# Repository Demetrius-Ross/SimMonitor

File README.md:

# SimMonitoring Overview WIP

Rename the main script to main.py
'''bash
mv espnow_sender_relay.py main.py
'''

Flash it to the ESP32:
'''bash
mpremote connect /dev/ttyUSB0 fs cp main.py :
'''

Reset the ESP32 to run it automatically:
'''bash
mpremote connect /dev/ttyUSB0 reset
'''

If you want manual execution, you can run any script interactively:
'''bash
mpremote connect /dev/ttyUSB0 run gpio_test.py
'''

## Wiring Guide for Each ESP32 Device

# ESP32 Device ID Configuration for Sender

Below is a quick reference for how to wire **GPIO17**, **GPIO16**, **GPIO4**, and **GPIO2** to assign a **device ID** (0–15). Each pin is interpreted as a bit in the 4-bit ID, read in the order `(Pin2=bit0, Pin4=bit1, Pin16=bit2, Pin17=bit3)`.

| Device ID | Binary (bit3..bit0) | Pin17 (bit3) | Pin16 (bit2) | Pin4 (bit1) | Pin2 (bit0) |
|-----------|----------------------|--------------|--------------|-------------|-------------|
| **0**     | `0000`              | 0 (LOW)      | 0 (LOW)      | 0 (LOW)     | 0 (LOW)     |
| **1**     | `0001`              | 0 (LOW)      | 0 (LOW)      | 0 (LOW)     | 1 (HIGH)    |
| **2**     | `0010`              | 0 (LOW)      | 0 (LOW)      | 1 (HIGH)    | 0 (LOW)     |
| **3**     | `0011`              | 0 (LOW)      | 0 (LOW)      | 1 (HIGH)    | 1 (HIGH)    |
| **4**     | `0100`              | 0 (LOW)      | 1 (HIGH)     | 0 (LOW)     | 0 (LOW)     |
| **5**     | `0101`              | 0 (LOW)      | 1 (HIGH)     | 0 (LOW)     | 1 (HIGH)    |
| **6**     | `0110`              | 0 (LOW)      | 1 (HIGH)     | 1 (HIGH)    | 0 (LOW)     |
| **7**     | `0111`              | 0 (LOW)      | 1 (HIGH)     | 1 (HIGH)    | 1 (HIGH)    |
| **8**     | `1000`              | 1 (HIGH)     | 0 (LOW)      | 0 (LOW)     | 0 (LOW)     |
| **9**     | `1001`              | 1 (HIGH)     | 0 (LOW)      | 0 (LOW)     | 1 (HIGH)    |
| **10**    | `1010`              | 1 (HIGH)     | 0 (LOW)      | 1 (HIGH)    | 0 (LOW)     |
| **11**    | `1011`              | 1 (HIGH)     | 0 (LOW)      | 1 (HIGH)    | 1 (HIGH)    |
| **12**    | `1100`              | 1 (HIGH)     | 1 (HIGH)     | 0 (LOW)     | 0 (LOW)     |
| **13**    | `1101`              | 1 (HIGH)     | 1 (HIGH)     | 0 (LOW)     | 1 (HIGH)    |
| **14**    | `1110`              | 1 (HIGH)     | 1 (HIGH)     | 1 (HIGH)    | 0 (LOW)     |
| **15**    | `1111`              | 1 (HIGH)     | 1 (HIGH)     | 1 (HIGH)    | 1 (HIGH)    |

## Notes

1. **GPIO2** is the **least significant bit** (bit0).  
2. **GPIO17** is the **most significant bit** (bit3).  
3. Use **10kΩ resistors** (or internal pulls) to pull each pin HIGH or LOW.  
4. For a **Sender** role, set **GPIO18 = 0 (LOW)** and **GPIO19 = 0 (LOW)**. This yields `role_value = 0` => `"SENDER"`.

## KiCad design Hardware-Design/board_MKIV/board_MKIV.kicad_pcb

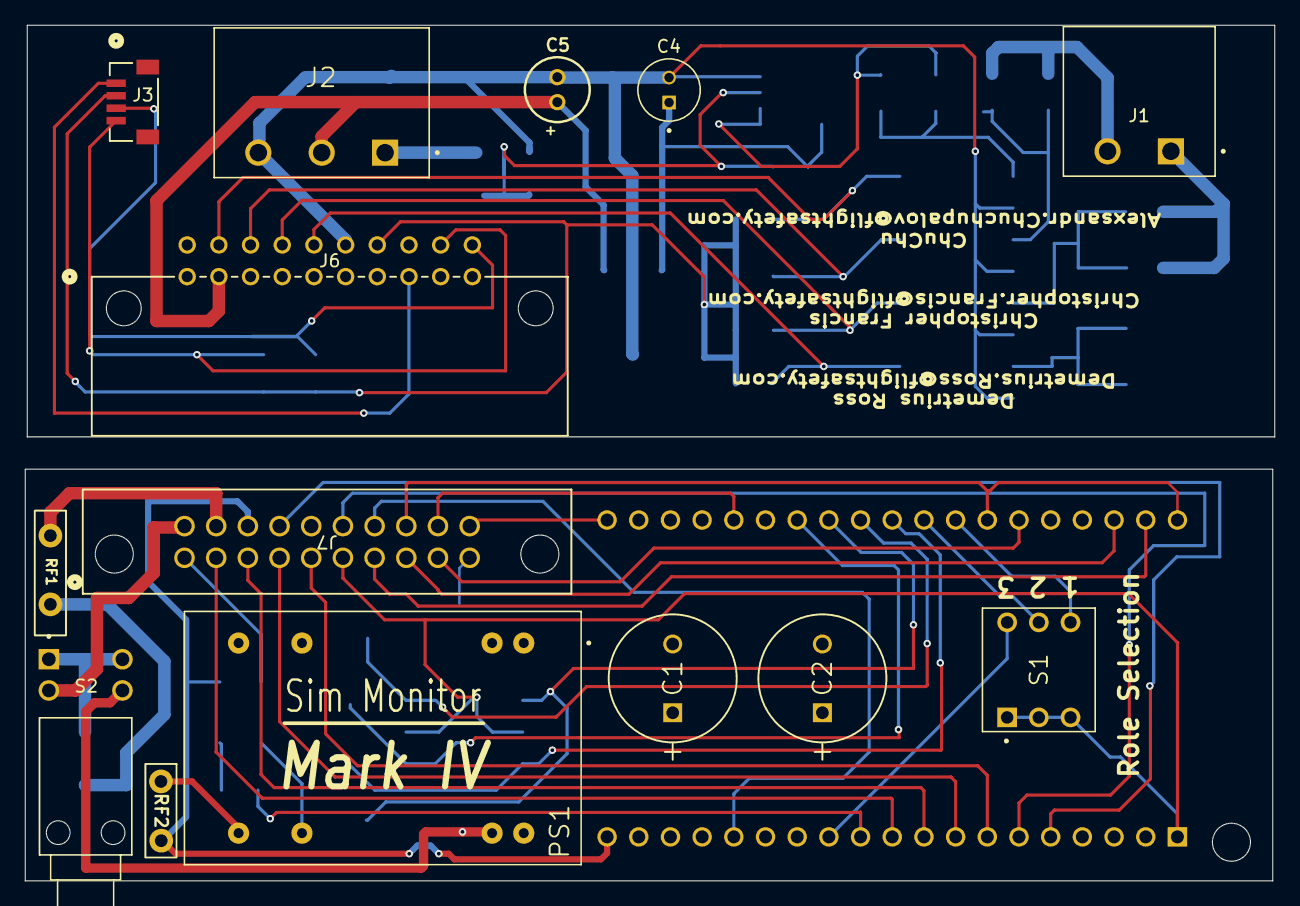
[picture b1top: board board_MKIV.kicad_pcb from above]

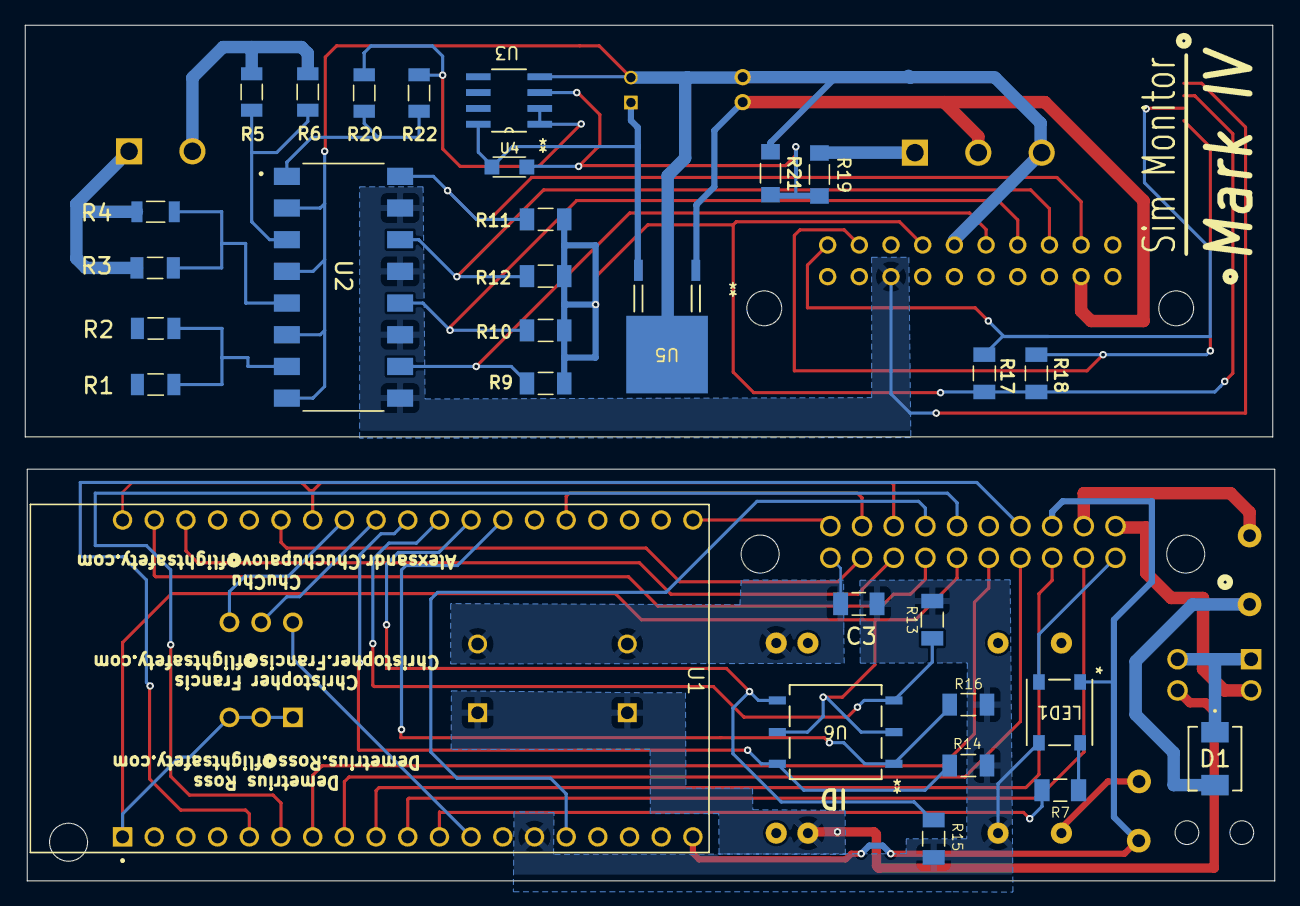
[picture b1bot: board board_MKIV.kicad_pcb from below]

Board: 2 copper layers, 100.2 x 68.6 mm, 44 parts (30 on the bottom side), 40 nets.

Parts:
C1, C2: UHE2A470MPD; PCAP_10x12_5-THRU-ELECT_NCA
C3: 1000pf/3kV; CAPC3216X180N
C4: ECA1HM100; CAPPRD200W50D500H1100
C5: WCAP-ATG5_5X11; WCAP-ATG5_5X11_DXL_
D1: SS34B-HF; DO214AASMB_CIP-L
J1: 1757242; PHOENIX_1757242
J2: jst-power; PHOENIX_1757255
J3: JST -SM; CONN_BM04B-SRSS-TB_SPK
J6: 20_pin_90
J7: 20-pin-straight; 20_pin_straight
LED1: COM-16347; COM-16347_SPK
PS1: REC5A-2405SW_H2; CONV_REC5A-2405SW_H2
R1, R2, R3, R5, R6: CRGH1206J4K7; RESC3115X65N
R4: CRGH1206J4K7; RESC3015X65N
R7: CRL1206-FW-R330ELF; RESC3216X70N
R9, R10, R11, R12, R13, R14, R15, R16, R17, R18: CR1206-FX-1002ELF; RESC3216X75N
R19: ERJP08J105V; RES_ERJP08J105V
R20, R22: CRG1206F470R; RESC3115X65N
R21: ERJP08J334V; RES_ERJP08J334V
RF1, RF2: PTC_RESET_FUSE
S1: DS01C-254-S-03BE; SW_DS01C-254-S-03BE
S2: PB400EEQR1BLK; SW_PB400EEQR1BLK
U1: ESP32-DEVKITC-32D; MODULE_ESP32-DEVKITC-32D
U2: LTV-846S; SOIC254P1016X460-16N
U3: TLV272CDR; D8
U4: BAT46W; SOD123F
U5: BA&; TO252-3_ROM
U6: SH-7070TB; SH-7070TB_7P1X7P3_NDC

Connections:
+3.3V: J3.2, J6.B7, J7.6, R9.2, R10.2, R11.2, R12.2, R17.1, R18.1, S1.1A, S1.2A, S1.3A, U1.J2-1 (3V3), U6.2, U6.5
+24V: D1.1, S2.1, S2.3
+VIN: C1.1, C2.1, D1.2, J6.A1, J7.11, PS1.22 (+VIN), RF1.2, S2.2, S2.4
+VIN-dc: C5.1, J2.02, J6.A2, J7.12, RF1.1, U5.1 (INPUT)
+VOUT_esp_signal: J6.A3, J7.13, LED1.1 (VDD), RF2.2, U1.J2-19 (EXT_5V)
-Vin: C1.2, C2.2, C3.2, C4.N, C5.2, J2.03, J6.B6, J7.10, PS1.2 (-VIN), R21.1, U2.2, U2.4, U2.6, U2.8, U3.4 (GND), U5.2 (Common)
/ESP-Board/+VOUT: PS1.14 (+VOUT), RF2.1
/ramp_down_opto: R5.2, R6.2, U2.3
/sim_home_opto: R20.2, R22.2, U2.1
CLK: J6.A10, J7.20, U1.J3-19 (CLK)
ESP_GND2: C3.1, J3.1, J6.A8, J7.18, LED1.3 (VSS), PS1.16 (-VOUT), R13.2, R14.2, R15.2, R16.2, U1.J2-14 (GND1), U1.J3-1 (GND3), U1.J3-7 (GND2), U2.9, U2.11, U2.13, U2.15
GPIO_2: J6.A9, J7.19, U1.J3-15 (IO2)
GPIO_4: R16.1, U1.J3-13 (IO4), U6.1
GPIO_5: R14.1, U1.J3-10 (IO5), U6.6
GPIO_13: J6.A7, J7.17, U1.J2-15 (IO13)
GPIO_14: S1.1B, U1.J2-12 (IO14)
GPIO_16: R15.1, U1.J3-12 (IO16), U6.4
GPIO_17: R13.1, U1.J3-11 (IO17), U6.3
GPIO_18: S1.2B, U1.J3-9 (IO18)
GPIO_19: S1.3B, U1.J3-8 (IO19)
GPIO_21: J3.3, J6.B10, J7.9, R17.2, U1.J3-6 (IO21)
GPIO_22: J3.4, J6.B9, J7.8, R18.2, U1.J3-3 (IO22)
GPIO_23: J6.B8, J7.7, U1.J3-2 (IO23)
GPIO_25: J6.B3, J7.3, R12.1, U1.J2-9 (IO25), U2.14
GPIO_26: J6.B2, J7.2, R11.1, U1.J2-10 (IO26), U2.16
GPIO_27: J6.B1, J7.1, LED1.2 (DOUT), R7.2, U1.J2-11 (IO27)
GPIO_32: J6.B5, J7.5, R9.1, U1.J2-7 (IO32), U2.10
GPIO_33: J6.B4, J7.4, R10.1, U1.J2-8 (IO33), U2.12
GPIO_ANAG_34: J6.A4, J7.14, U1.J2-5 (IO34)
GPIO_ANAG_35: J6.A6, J7.16, U1.J2-6 (IO35)
unnamed: LED1.4 (DIN), R7.1
unnamed: R19.1, R21.2, U3.3 (1IN+), U4.2
VDD: C4.P, U3.8 (VDD), U4.1, U5.3 (OUTPUT)
ramp_down: J1.02, R5.1, R6.1
ramp_up: J1.01, R3.1, R4.1
ramp_up_opto: R3.2, R4.2, U2.5
sim_home: J2.01, R19.2
sim_home_safe: R20.1, R22.1, U3.1 (1OUT), U3.2 (1IN-)
spare: R1.1, R2.1
spare_opto: R1.2, R2.2, U2.7

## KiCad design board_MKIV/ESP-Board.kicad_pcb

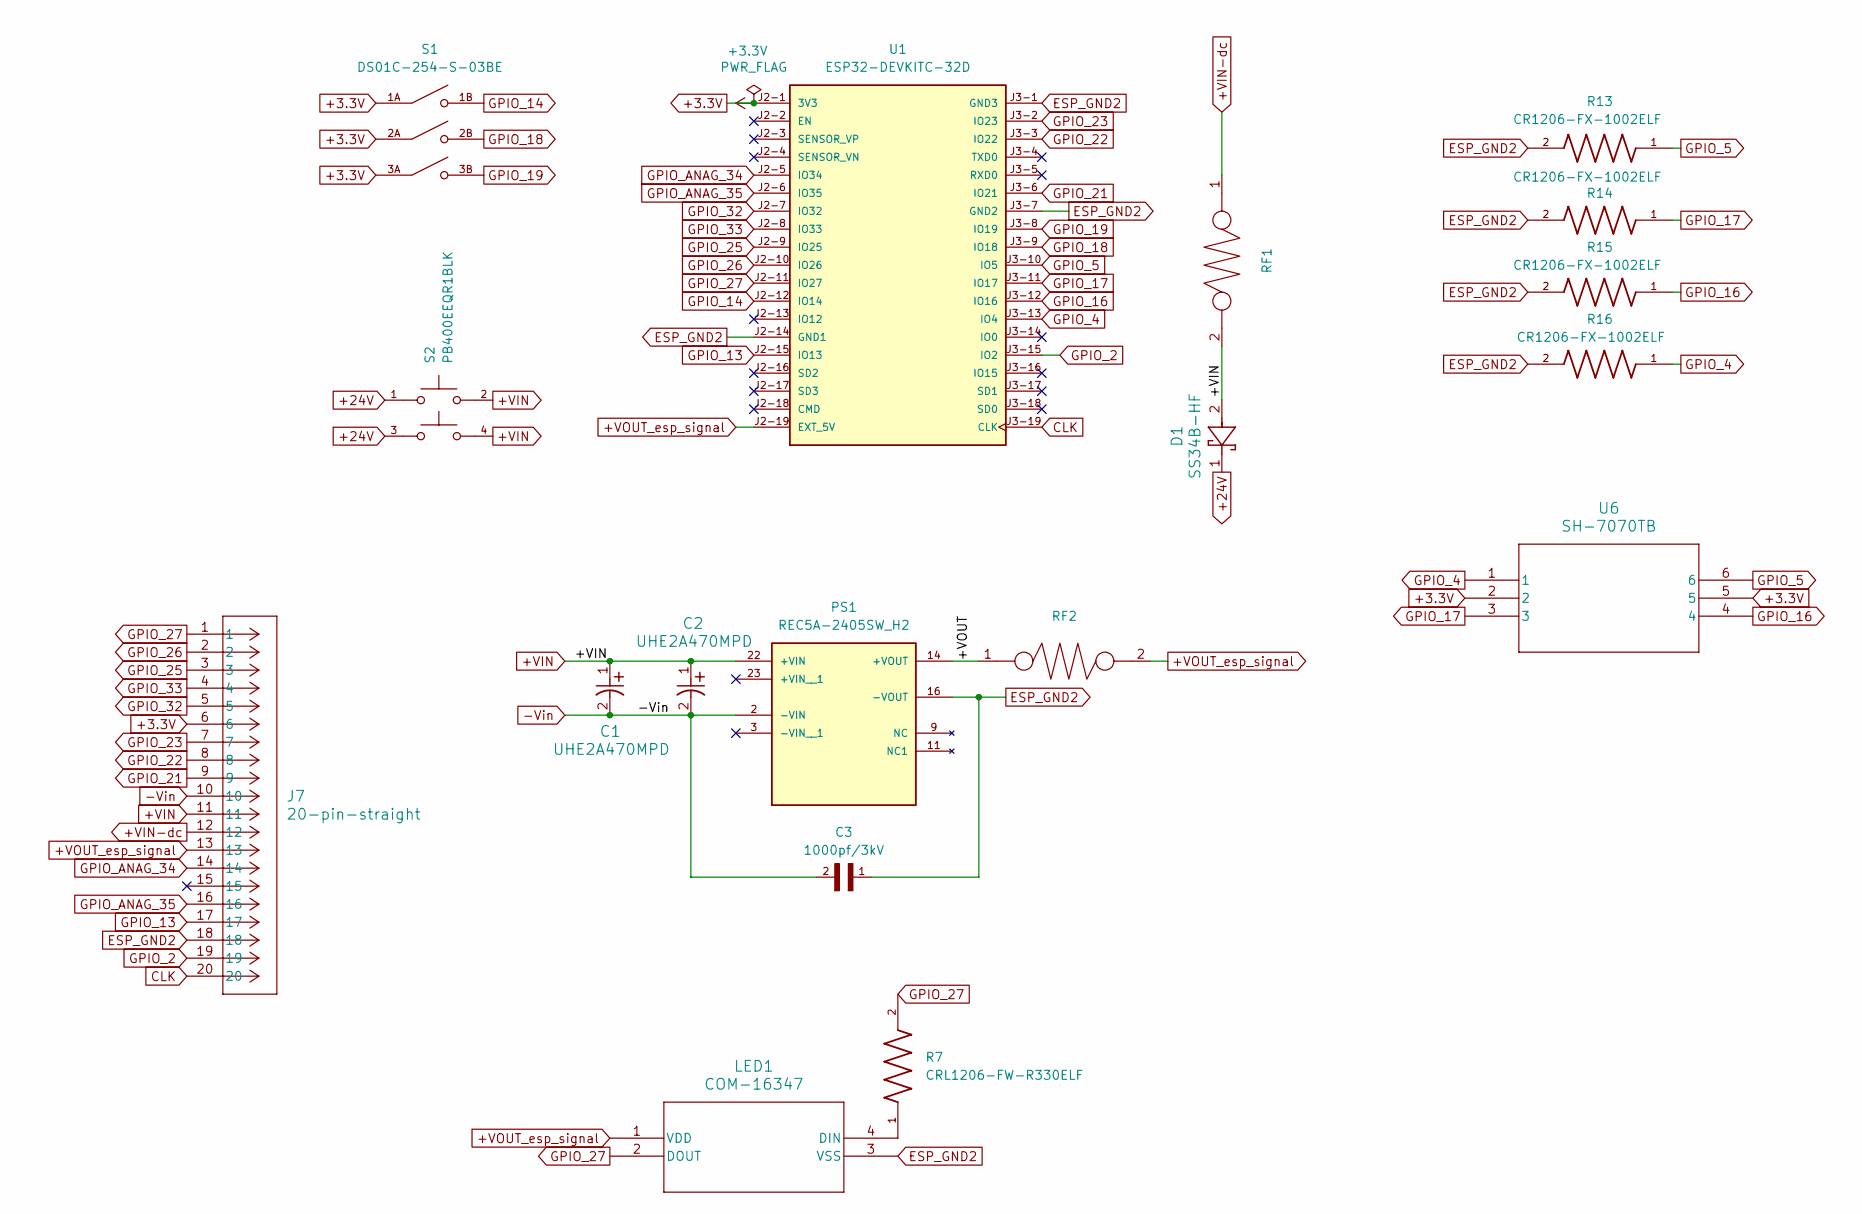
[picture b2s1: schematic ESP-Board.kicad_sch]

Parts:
C1, C2: UHE2A470MPD; PCAP_10x12_5-THRU-ELECT_NCA
C3: 1000pf/3kV; CAPC3216X180N
D1: SS34B-HF; DO214AASMB_CIP-L
J7: 20-pin-straight; 20_pin_straight
LED1: COM-16347; COM-16347_SPK
PS1: REC5A-2405SW_H2; CONV_REC5A-2405SW_H2; PARTREV N/A
R7: CRL1206-FW-R330ELF; RESC3216X70N
R13, R14, R15, R16: CR1206-FX-1002ELF; RESC3216X75N
RF1, RF2: PTC_RESET_FUSE
S1: DS01C-254-S-03BE; SW_DS01C-254-S-03BE; PARTREV 1.0
S2: PB400EEQR1BLK; SW_PB400EEQR1BLK; PARTREV A
U1: ESP32-DEVKITC-32D; MODULE_ESP32-DEVKITC-32D; PARTREV V4
U6: SH-7070TB; SH-7070TB_7P1X7P3_NDC

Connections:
+3.3V: J7.6, S1.1A, S1.2A, S1.3A, U1.J2-1 (3V3), U6.2, U6.5
+24V: D1.1, S2.1, S2.3
+VIN: C1.1, C2.1, D1.2, J7.11, PS1.22 (+VIN), RF1.2, S2.2, S2.4
+VIN-dc: J7.12, RF1.1
+VOUT_esp_signal: J7.13, LED1.1 (VDD), RF2.2, U1.J2-19 (EXT_5V)
-Vin: C1.2, C2.2, C3.2, J7.10, PS1.2 (-VIN)
/ESP-Board/+VOUT: PS1.14 (+VOUT), RF2.1
CLK: J7.20, U1.J3-19 (CLK)
ESP_GND2: C3.1, J7.18, LED1.3 (VSS), PS1.16 (-VOUT), R13.2, R14.2, R15.2, R16.2, U1.J2-14 (GND1), U1.J3-1 (GND3), U1.J3-7 (GND2)
GPIO_2: J7.19, U1.J3-15 (IO2)
GPIO_4: R16.1, U1.J3-13 (IO4), U6.1
GPIO_5: R14.1, U1.J3-10 (IO5), U6.6
GPIO_13: J7.17, U1.J2-15 (IO13)
GPIO_14: S1.1B, U1.J2-12 (IO14)
GPIO_16: R15.1, U1.J3-12 (IO16), U6.4
GPIO_17: R13.1, U1.J3-11 (IO17), U6.3
GPIO_18: S1.2B, U1.J3-9 (IO18)
GPIO_19: S1.3B, U1.J3-8 (IO19)
GPIO_21: J7.9, U1.J3-6 (IO21)
GPIO_22: J7.8, U1.J3-3 (IO22)
GPIO_23: J7.7, U1.J3-2 (IO23)
GPIO_25: J7.3, U1.J2-9 (IO25)
GPIO_26: J7.2, U1.J2-10 (IO26)
GPIO_27: J7.1, LED1.2 (DOUT), R7.2, U1.J2-11 (IO27)
GPIO_32: J7.5, U1.J2-7 (IO32)
GPIO_33: J7.4, U1.J2-8 (IO33)
GPIO_ANAG_34: J7.14, U1.J2-5 (IO34)
GPIO_ANAG_35: J7.16, U1.J2-6 (IO35)
unnamed: LED1.4 (DIN), R7.1

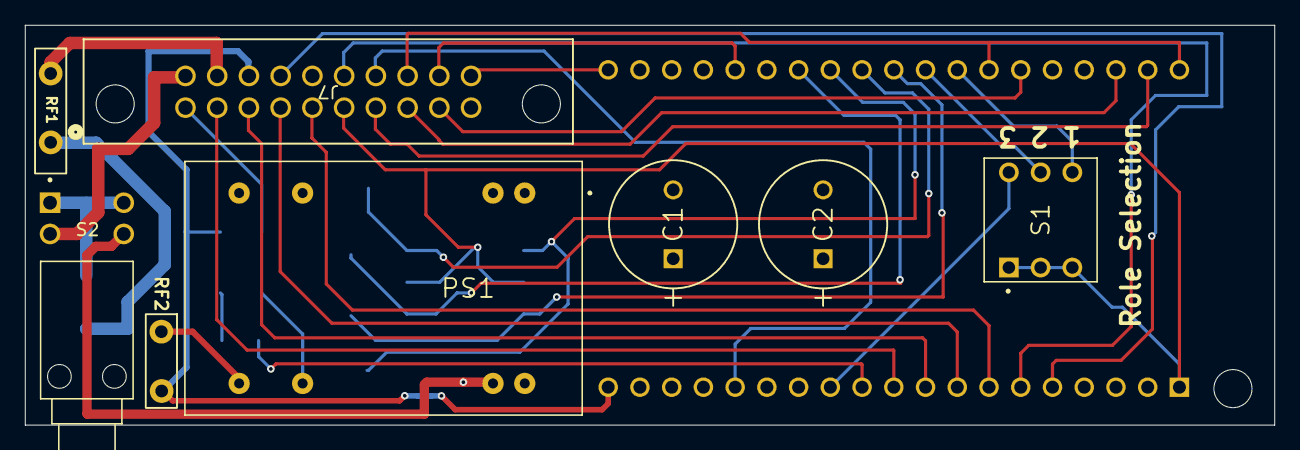
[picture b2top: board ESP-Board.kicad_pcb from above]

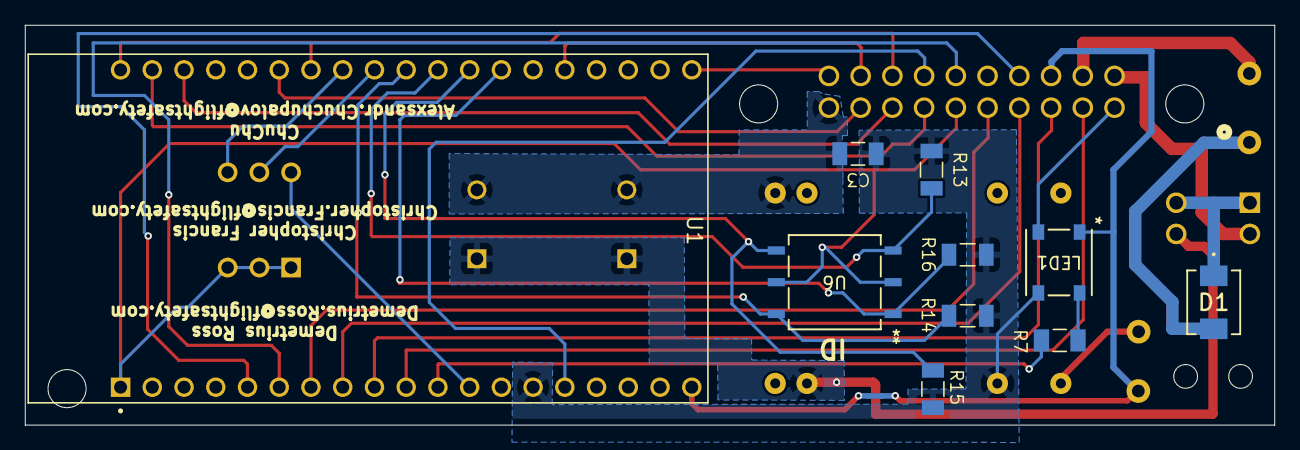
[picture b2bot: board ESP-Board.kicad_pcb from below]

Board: 2 copper layers, 100.0 x 32.0 mm, 18 parts (10 on the bottom side), 29 nets.

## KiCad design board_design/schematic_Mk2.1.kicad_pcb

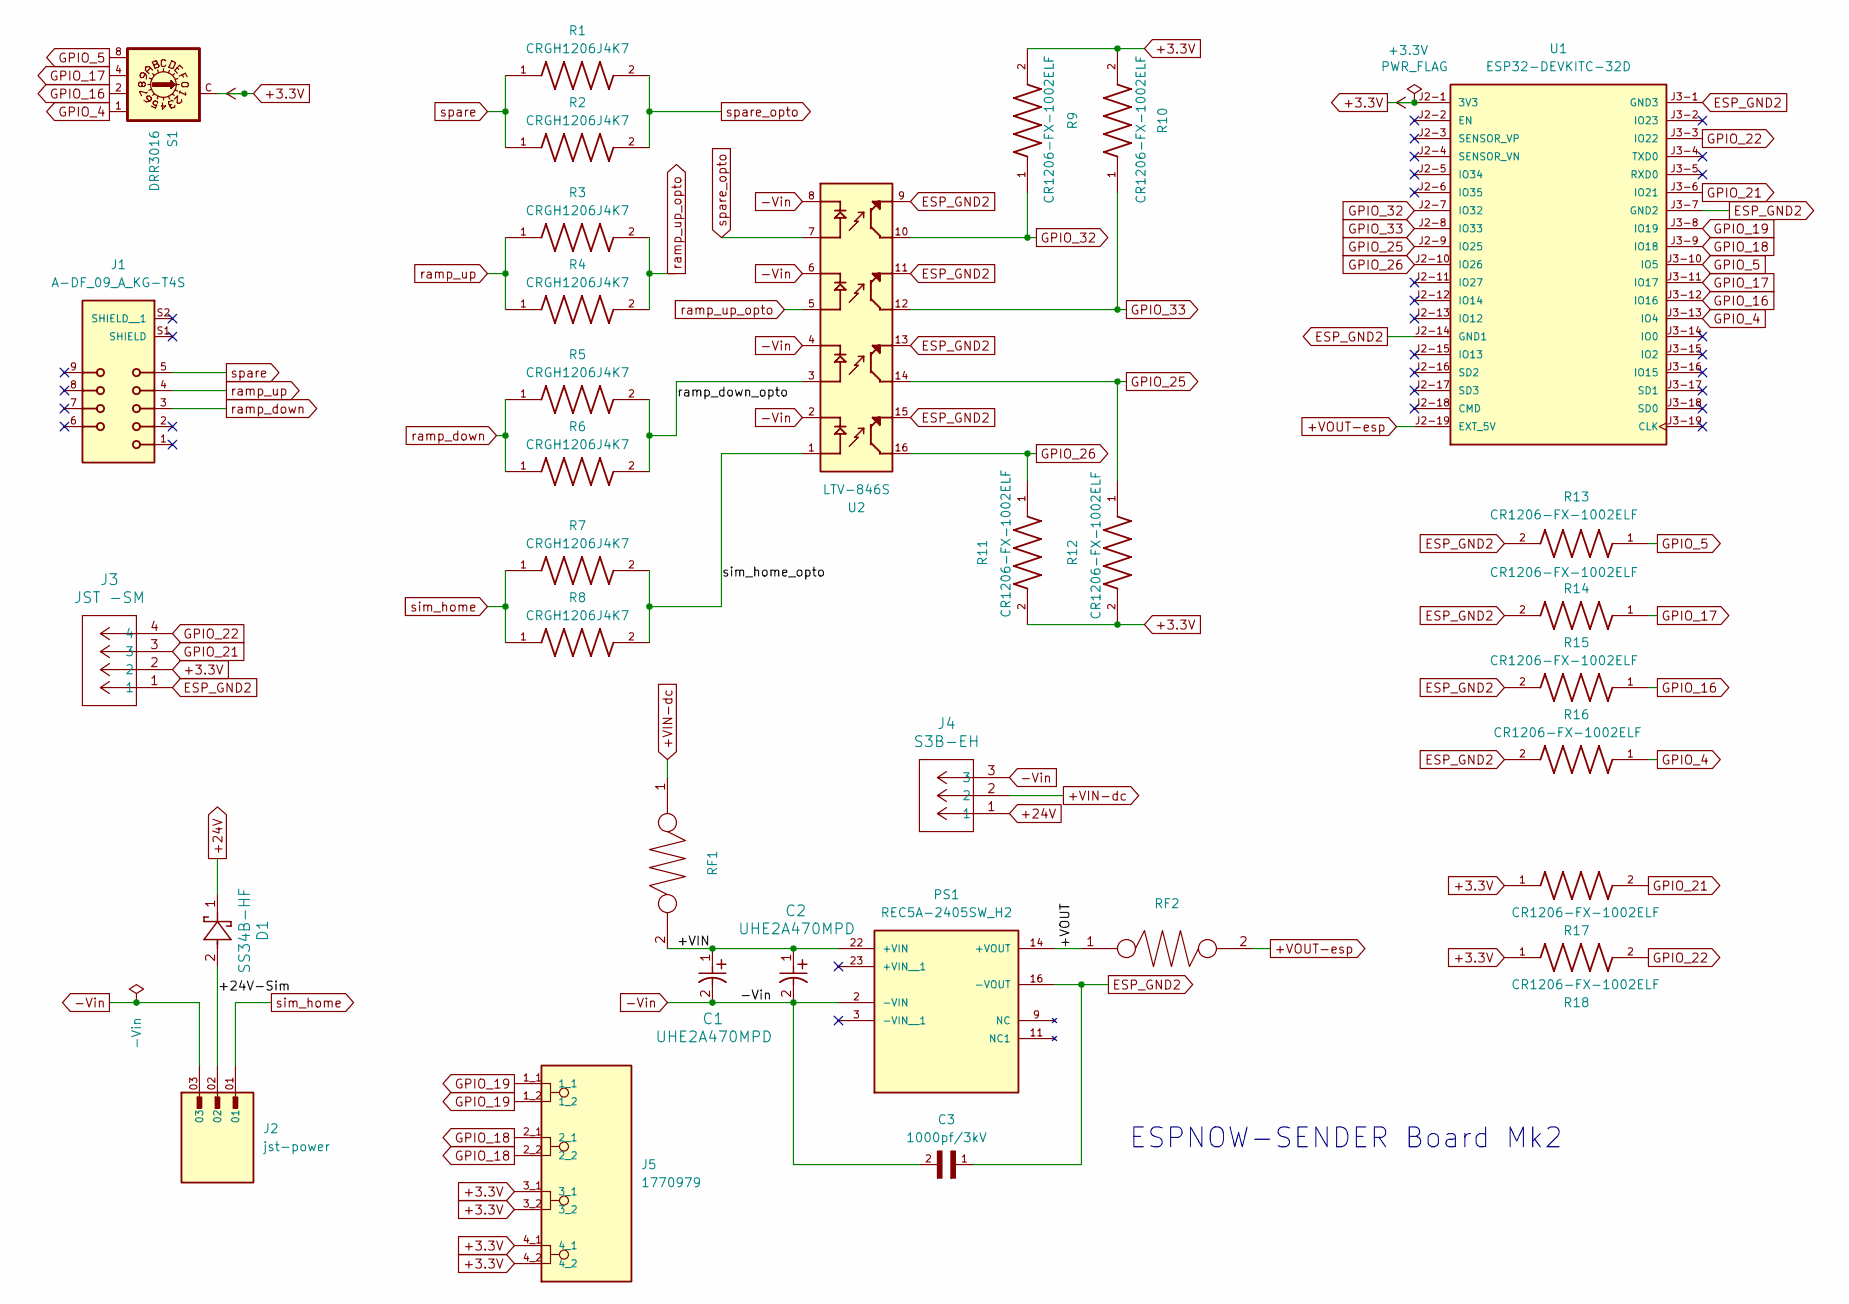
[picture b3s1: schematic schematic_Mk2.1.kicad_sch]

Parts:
C1, C2: UHE2A470MPD; PCAP_10x12_5-THRU-ELECT_NCA
C3: 1000pf/3kV; CAPC3216X180N
D1: SS34B-HF; DO214AASMB_CIP-L
J1: A-DF_09_A_KG-T4S; ASSMANN_A-DF_09_A_KG-T4S; PARTREV 05
J2: jst-power; PHOENIX_1757255; PARTREV 28.07.2023
J3: JST -SM; CONN_BM04B-SRSS-TB_SPK
J4: S3B-EH; CONN_S3B-EH_JST
J5: 1770979; PHOENIX_1770979
PS1: REC5A-2405SW_H2; CONV_REC5A-2405SW_H2; PARTREV N/A
R1, R2, R3, R5, R6, R7, R8: CRGH1206J4K7; RESC3115X65N
R4: CRGH1206J4K7; RESC3015X65N
R9, R10, R11, R12, R13, R14, R15, R16, R17, R18: CR1206-FX-1002ELF; RESC3216X75N
RF1, RF2: PTC_RESET_FUSE
S1: DRR3016; DRR3010; MPN DRR3016
U1: ESP32-DEVKITC-32D; MODULE_ESP32-DEVKITC-32D; PARTREV V4
U2: LTV-846S; SOIC254P1016X460-16N; PARTREV H

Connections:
+3.3V: J3.2, J5.3_1, J5.3_2, J5.4_1, J5.4_2, R9.2, R10.2, R11.2, R12.2, R17.1, R18.1, S1.C, U1.J2-1 (3V3)
+24V: D1.1, J4.1
+VIN-dc: J4.2, RF1.1
+VOUT-esp: RF2.2, U1.J2-19 (EXT_5V)
-Vin: C1.2, C2.2, C3.2, J2.03, J4.3, PS1.2 (-VIN), U2.2, U2.4, U2.6, U2.8
/+24V-Sim: D1.2, J2.02
/+VIN: C1.1, C2.1, PS1.22 (+VIN), RF1.2
/+VOUT: PS1.14 (+VOUT), RF2.1
/ramp_down_opto: R5.2, R6.2, U2.3
/sim_home_opto: R7.2, R8.2, U2.1
ESP_GND2: C3.1, J3.1, PS1.16 (-VOUT), R13.2, R14.2, R15.2, R16.2, U1.J2-14 (GND1), U1.J3-1 (GND3), U1.J3-7 (GND2), U2.9, U2.11, U2.13, U2.15
GPIO_4: R16.1, S1.1, U1.J3-13 (IO4)
GPIO_5: R14.1, S1.8, U1.J3-10 (IO5)
GPIO_16: R15.1, S1.2, U1.J3-12 (IO16)
GPIO_17: R13.1, S1.4, U1.J3-11 (IO17)
GPIO_18: J5.2_1, J5.2_2, U1.J3-9 (IO18)
GPIO_19: J5.1_1, J5.1_2, U1.J3-8 (IO19)
GPIO_21: J3.3, R17.2, U1.J3-6 (IO21)
GPIO_22: J3.4, R18.2, U1.J3-3 (IO22)
GPIO_25: R12.1, U1.J2-9 (IO25), U2.14
GPIO_26: R11.1, U1.J2-10 (IO26), U2.16
GPIO_32: R9.1, U1.J2-7 (IO32), U2.10
GPIO_33: R10.1, U1.J2-8 (IO33), U2.12
ramp_down: J1.3, R5.1, R6.1
ramp_up: J1.4, R3.1, R4.1
ramp_up_opto: R3.2, R4.2, U2.5
sim_home: J2.01, R7.1, R8.1
spare: J1.5, R1.1, R2.1
spare_opto: R1.2, R2.2, U2.7

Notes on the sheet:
ESPNOW-SENDER Board Mk2

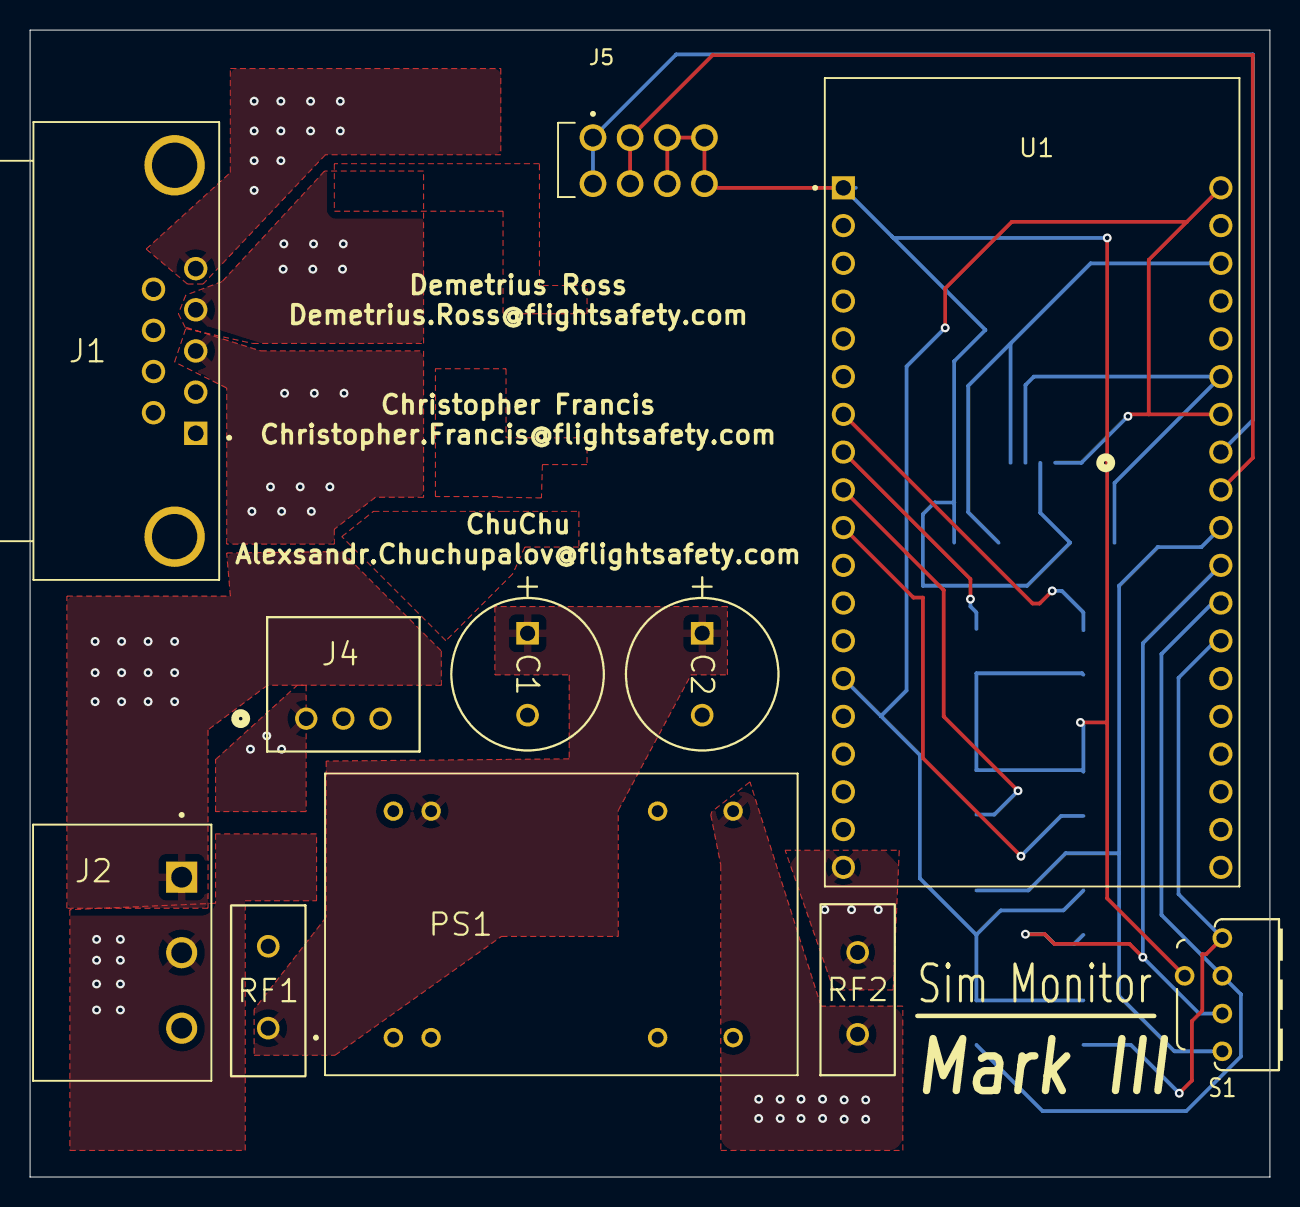
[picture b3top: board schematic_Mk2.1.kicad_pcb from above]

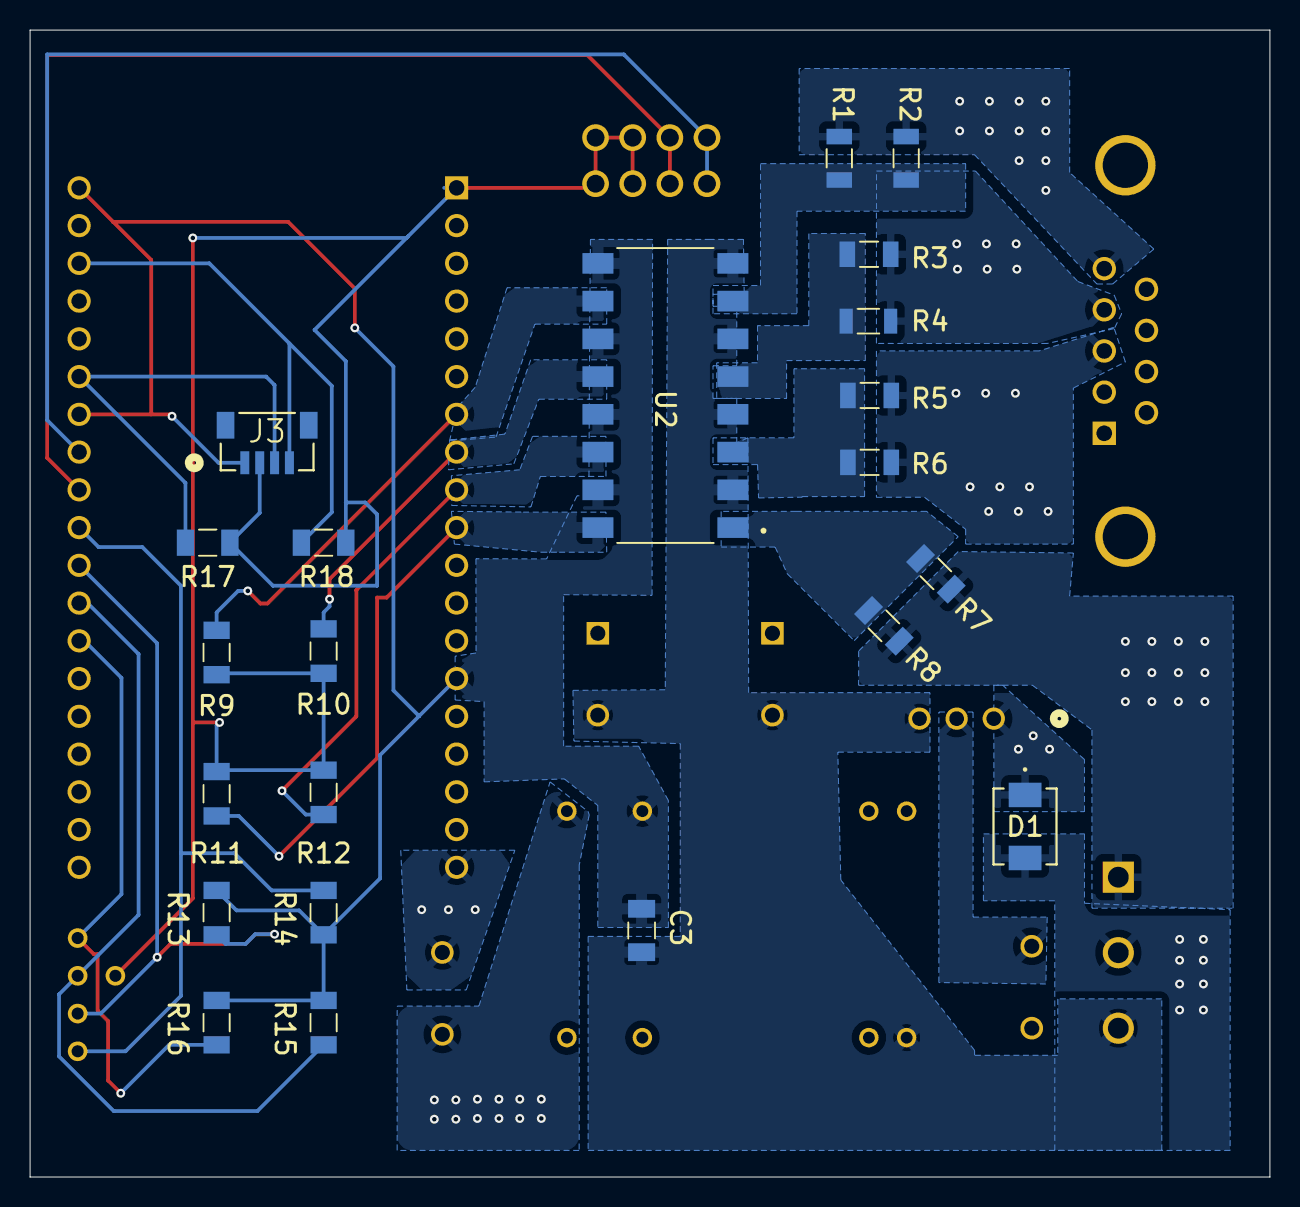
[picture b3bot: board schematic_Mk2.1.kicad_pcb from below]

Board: 2 copper layers, 83.4 x 77.2 mm, 33 parts (22 on the bottom side), 29 nets.

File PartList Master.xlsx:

Sim Monitor Board Component List
Part | DigiKey Name | QTY | Price Per Component | Total Price of Item | Link | Notes
4.7 kOhms Chip Resistor | CRGH1206J4K7 | 8 | 0.14000000000000001 | 1.1200000000000001 | CRGH1206J4K7 TE Connectivity Passive Product | Resistors | DigiKey
10 kOhm Chip Resistor | CR1206-FX-1002ELF | 10 | 0.1 | 1 | CR1206-FX-1002ELF Bourns Inc. | Resistors | DigiKey
Rotary Hex Switch | DRR3016 | 1 | 3.08 | 3.08 | DRR 3016 Knitter-Switch | Switches | DigiKey
Optocoupler | 160-1365-5-ND | 1 | 0.9 | 0.9 | LTV-846S Lite-On Inc. | Isolators | DigiKey
JST Connector Header | S3B-EH | 1 | 0.11 | 0.11 | S3B-EH JST Sales America Inc. | Connectors, Interconnects | DigiKey
Schottky Diode | SS34B-HF | 1 | 0.27 | 0.27 | SS34B-HF Comchip Technology | Discrete Semiconductor Products | DigiKey
1000 pF (3kV) Ceramic Cap | VPDD302W102K1GV001E | 1 | 0.57999999999999996 | 0.57999999999999996 | VPDD302W102K1GV001E Johanson Dielectrics Inc. | Capacitors | DigiKey
QWIIC Connector Header | 1568-16766-ND | 1 | 0.75 | 0.75 | 16766 SparkFun Electronics | Connectors, Interconnects | DigiKey
JST Female Socket | 455-2935-ND | 1 | 0.18 | 0.18 | 03HR-4K-P-N JST Sales America Inc. | Connectors, Interconnects | DigiKey
47 uF (100V) Electrolytic Cap | UHE2A470MPD | 2 | 0.56000000000000005 | 1.1200000000000001 | UHE2A470MPD Nichicon | Capacitors | DigiKey
D-Sub Female Through Hole | A-DF 09 A/KG-T4S | 1 | 0.72 | 0.72 | A-DF 09 A/KG-T4S Assmann WSW Components | Connectors, Interconnects | DigiKey
3 Pos Male Block Header | 1757255 | 1 | 1.26 | 1.26 | 1757255 Phoenix Contact | Connectors, Interconnects | DigiKey
ISO DC-DC Converter 5V | REC5A-2405SW/H2 | 1 | 14.82 | 14.82 | REC5A-2405SW/H2 Recom Power | Power Supplies - Board Mount | DigiKey
PTC Reset Fuse 1.1 A | RXEF110-ND | 1 | 0.56000000000000005 | 0.56000000000000005 | RXEF110 Littelfuse Inc. | Circuit Protection | DigiKey | Backorder
PTC Reset Fuse 500 mA | RXEF050-2HFCT-ND | 1 | 0.54 | 0.54 | RXEF050-2 Littelfuse Inc. | Circuit Protection | DigiKey
ESP32 | ESP32-DEVKITC-32E | 1 | 10 | 10 | ESP32-DEVKITC-32E Espressif Systems | Development Boards, Kits, Programmers | D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
Total Cost of Components |  |  |  | 37.01
Board Cost (PCB Way @ 10 Boards) |  | QTY: 1 | 0.65
Total |  |  |  | 37.659999999999997

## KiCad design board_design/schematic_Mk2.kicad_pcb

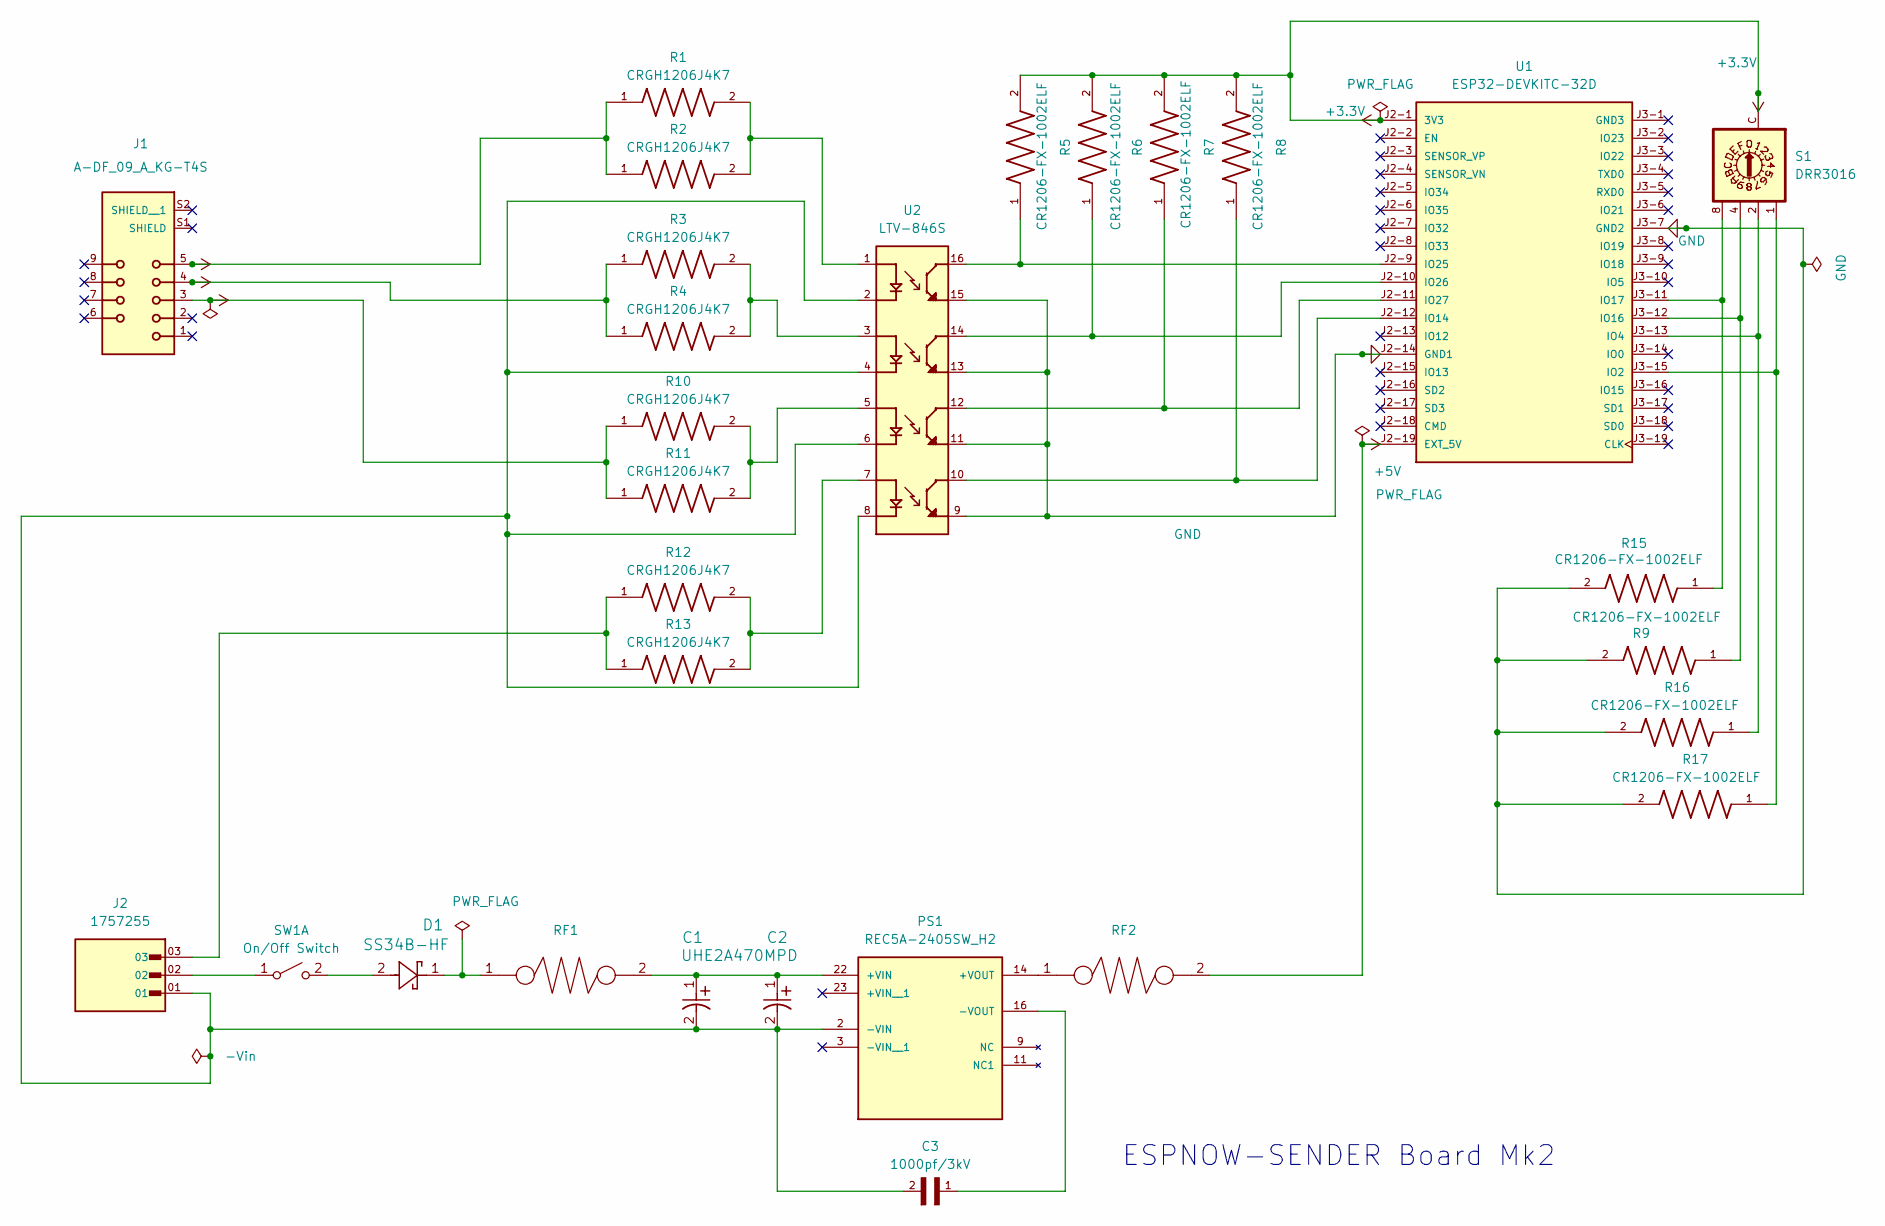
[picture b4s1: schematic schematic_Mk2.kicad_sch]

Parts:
C1, C2: UHE2A470MPD; PCAP_10x12_5-THRU-ELECT_NCA
C3: 1000pf/3kV; CAPC3216X180N
D1: SS34B-HF; DO214AASMB_CIP-L
J1: A-DF_09_A_KG-T4S; ASSMANN_A-DF_09_A_KG-T4S; PARTREV 05
J2: 1757255; PHOENIX_1757255; PARTREV 28.07.2023
PS1: REC5A-2405SW_H2; CONV_REC5A-2405SW_H2; PARTREV N/A
R1, R2, R3, R10, R11, R12, R13: CRGH1206J4K7; RESC3115X65N
R4: CRGH1206J4K7; RESC3015X65N
R5, R6, R7, R8, R9, R15, R16, R17: CR1206-FX-1002ELF; RESC3216X75N
RF1, RF2: PTC_RESET_FUSE
S1: DRR3016; DRR3010; MPN DRR3016
SW1: On/Off Switch; Panasonic_EVQPUJ_EVQPUA
U1: ESP32-DEVKITC-32D; MODULE_ESP32-DEVKITC-32D; PARTREV V4
U2: LTV-846S; SOIC254P1016X460-16N; PARTREV H

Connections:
+3.3V: R5.2, R6.2, R7.2, R8.2, S1.C, U1.J2-1 (3V3)
+5V: RF2.2, U1.J2-19 (EXT_5V)
+24V: J1.3, J1.4, J1.5, R1.1, R2.1, R3.1, R4.1, R10.1, R11.1
GND: R9.2, R15.2, R16.2, R17.2, U1.J2-14 (GND1), U1.J3-7 (GND2), U2.9, U2.11, U2.13, U2.15
unnamed: D1.1, RF1.1
unnamed: J2.03, R12.1, R13.1
unnamed: C1.1, C2.1, PS1.22 (+VIN), RF1.2
unnamed: PS1.14 (+VOUT), RF2.1
unnamed: C1.2, C2.2, C3.2, J2.01, PS1.2 (-VIN), U2.2, U2.4, U2.6, U2.8
unnamed: C3.1, PS1.16 (-VOUT)
unnamed: R1.2, R2.2, U2.1
unnamed: R3.2, R4.2, U2.3
unnamed: R10.2, R11.2, U2.5
unnamed: R12.2, R13.2, U2.7
unnamed: J2.02, SW1.1 (A)
unnamed: D1.2, SW1.2 (B)
unnamed: R17.1, S1.1, U1.J3-15 (IO2)
unnamed: R16.1, S1.2, U1.J3-13 (IO4)
unnamed: R8.1, U1.J2-12 (IO14), U2.10
unnamed: R15.1, S1.4, U1.J3-12 (IO16)
unnamed: R9.1, S1.8, U1.J3-11 (IO17)
unnamed: R5.1, U1.J2-9 (IO25), U2.16
unnamed: R6.1, U1.J2-10 (IO26), U2.14
unnamed: R7.1, U1.J2-11 (IO27), U2.12

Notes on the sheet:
ESPNOW-SENDER Board Mk2

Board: 2 copper layers, 29 parts (0 on the bottom side), 24 nets, no tracks yet.

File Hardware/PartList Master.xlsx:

Sim Monitor Board Component List
Part | DigiKey Name | QTY | Price Per Component | Total Price of Item | Link | Notes
4.7 kOhms Chip Resistor | CRGH1206J4K7 | 8 | 0.14000000000000001 | 1.1200000000000001 | CRGH1206J4K7 TE Connectivity Passive Product | Resistors | DigiKey
10 kOhm Chip Resistor | CR1206-FX-1002ELF | 10 | 0.1 | 1 | CR1206-FX-1002ELF Bourns Inc. | Resistors | DigiKey
Rotary Hex Switch | DRR3016 | 1 | 3.08 | 3.08 | DRR 3016 Knitter-Switch | Switches | DigiKey
Optocoupler | 160-1365-5-ND | 1 | 0.9 | 0.9 | LTV-846S Lite-On Inc. | Isolators | DigiKey
JST Connector Header | S3B-EH | 1 | 0.11 | 0.11 | S3B-EH JST Sales America Inc. | Connectors, Interconnects | DigiKey
Schottky Diode | SS34B-HF | 1 | 0.27 | 0.27 | SS34B-HF Comchip Technology | Discrete Semiconductor Products | DigiKey
1000 pF (3kV) Ceramic Cap | VPDD302W102K1GV001E | 1 | 0.57999999999999996 | 0.57999999999999996 | VPDD302W102K1GV001E Johanson Dielectrics Inc. | Capacitors | DigiKey
QWIIC Connector Header | 1568-16766-ND | 1 | 0.75 | 0.75 | 16766 SparkFun Electronics | Connectors, Interconnects | DigiKey
JST Female Socket | 455-2935-ND | 1 | 0.18 | 0.18 | 03HR-4K-P-N JST Sales America Inc. | Connectors, Interconnects | DigiKey
47 uF (100V) Electrolytic Cap | UHE2A470MPD | 2 | 0.56000000000000005 | 1.1200000000000001 | UHE2A470MPD Nichicon | Capacitors | DigiKey
D-Sub Female Through Hole | A-DF 09 A/KG-T4S | 1 | 0.72 | 0.72 | A-DF 09 A/KG-T4S Assmann WSW Components | Connectors, Interconnects | DigiKey
3 Pos Male Block Header | 1757255 | 1 | 1.26 | 1.26 | 1757255 Phoenix Contact | Connectors, Interconnects | DigiKey
ISO DC-DC Converter 5V | REC5A-2405SW/H2 | 1 | 14.82 | 14.82 | REC5A-2405SW/H2 Recom Power | Power Supplies - Board Mount | DigiKey
PTC Reset Fuse 1.1 A | RXEF110-ND | 1 | 0.56000000000000005 | 0.56000000000000005 | RXEF110 Littelfuse Inc. | Circuit Protection | DigiKey | Backorder
PTC Reset Fuse 500 mA | RXEF050-2HFCT-ND | 1 | 0.54 | 0.54 | RXEF050-2 Littelfuse Inc. | Circuit Protection | DigiKey
ESP32 | ESP32-DEVKITC-32E | 1 | 10 | 10 | ESP32-DEVKITC-32E Espressif Systems | Development Boards, Kits, Programmers | D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
Total Cost of Components |  |  |  | 37.01
Board Cost (PCB Way @ 10 Boards) |  | QTY: 1 | 0.65
Total |  |  |  | 37.659999999999997
